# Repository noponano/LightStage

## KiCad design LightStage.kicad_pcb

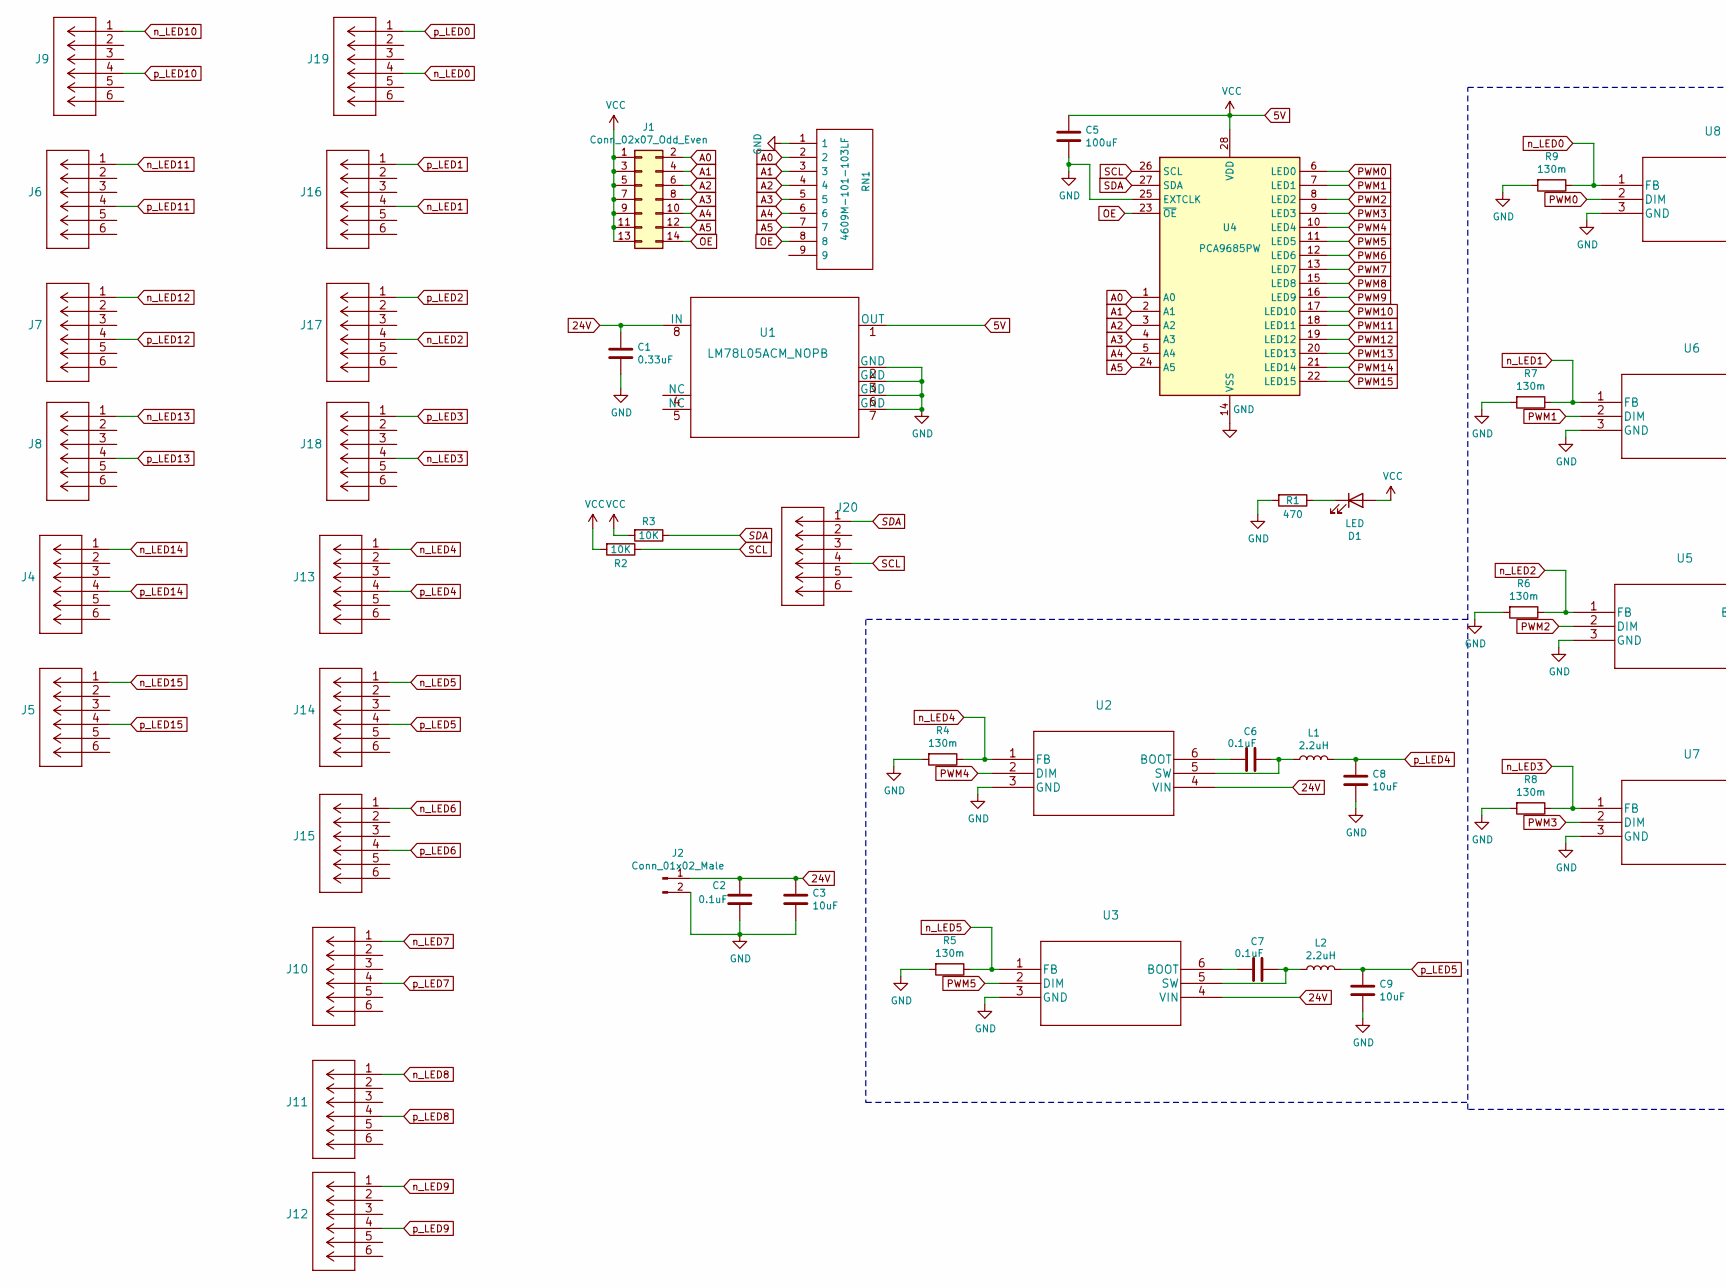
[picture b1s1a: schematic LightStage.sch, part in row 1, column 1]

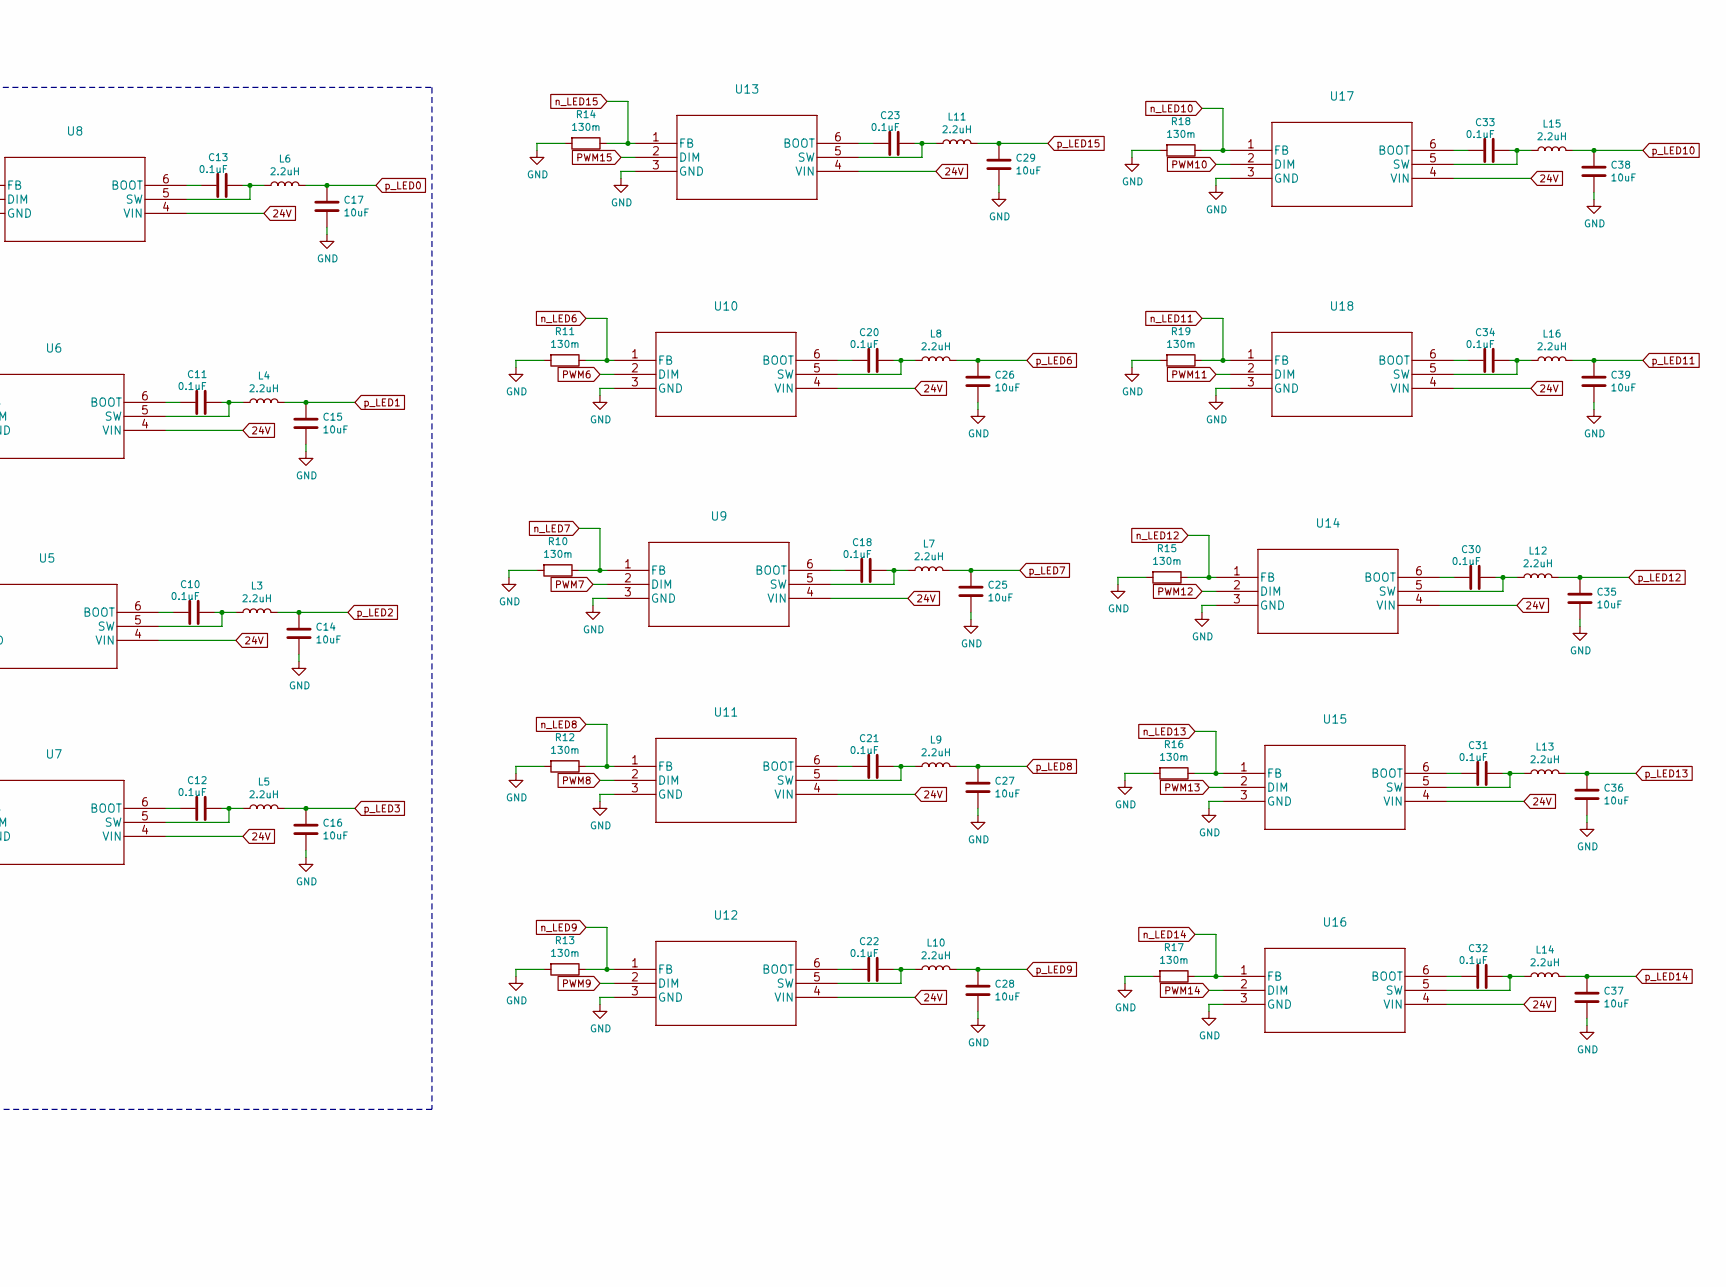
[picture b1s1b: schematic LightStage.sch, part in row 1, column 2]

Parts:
C1: 0.33uF; C_0805_2012Metric_Pad1.18x1.45mm_HandSolder
C2, C6, C7, C10, C11, C12, C13, C18, C20, C21, C22, C23, C30, C31, C32, C33, C34: 0.1uF; C_1206_3216Metric_Pad1.33x1.80mm_HandSolder
C3, C8, C9, C14, C15, C16, C17, C25, C26, C27, C28, C29, C35, C36, C37, C38, C39: 10uF; C_1206_3216Metric_Pad1.33x1.80mm_HandSolder
C5: 100uF; C_1206_3216Metric_Pad1.33x1.80mm_HandSolder
D1: LED; LED_0402_1005Metric_Pad0.77x0.64mm_HandSolder
J1: Conn_02x07_Odd_Even; PinHeader_2x07_P2.54mm_Vertical_SMD
J2: Conn_01x02_Male; Molex_26013114
J4, J5, J6, J7, J8, J9, J10, J11, J12, J13, J14, J15, J16, J17, J18, J19: 781710004
J20: 781710004
L1, L2, L3, L4, L5, L6, L7, L8, L9, L10, L11, L12, L13, L14, L15, L16: 2.2uH; L_0805_2012Metric_Pad1.15x1.40mm_HandSolder
R1: 470; R_0402_1005Metric_Pad0.72x0.64mm_HandSolder
R2, R3: 10K; R_0402_1005Metric_Pad0.72x0.64mm_HandSolder
R4, R5, R6, R7, R8, R9, R10, R11, R12, R13, R14, R15, R16, R17, R18, R19: 130m; R_0603_1608Metric_Pad0.98x0.95mm_HandSolder
RN1: 4609M-101-103LF; 4609X; Mouser Part Number 652-4609M-1LF-10K
U1: LM78L05ACM_NOPB; LM78L05ACM&slash_NOPB
U2, U3, U5, U6, U7, U8, U9, U10, U11, U12, U13, U14, U15, U16, U17, U18: TPS92200D2DDCR
U4: PCA9685PW; TSSOP-28_4.4x9.7mm_P0.65mm

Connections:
5V: C5.1, D1.2 (A), J1.1, J1.3, J1.5, J1.7, J1.9, J1.11, J1.13, R2.2, R3.2, U1.1 (OUT), U4.28 (VDD)
24V: C1.1, C2.1, C3.1, J2.1, U1.8 (IN), U2.4 (VIN), U3.4 (VIN), U5.4 (VIN), U6.4 (VIN), U7.4 (VIN), U8.4 (VIN), U9.4 (VIN), U10.4 (VIN), U11.4 (VIN), U12.4 (VIN), U13.4 (VIN), U14.4 (VIN), U15.4 (VIN), U16.4 (VIN), U17.4 (VIN), U18.4 (VIN)
A0: J1.2, RN1.2, U4.1 (A0)
A1: J1.4, RN1.3, U4.2 (A1)
A2: J1.6, RN1.4, U4.3 (A2)
A3: J1.8, RN1.5, U4.4 (A3)
A4: J1.10, RN1.6, U4.5 (A4)
A5: J1.12, RN1.7, U4.24 (A5)
GND: C1.2, C2.2, C3.2, C5.2, C8.2, C9.2, C14.2, C15.2, C16.2, C17.2, C25.2, C26.2, C27.2, C28.2, C29.2, C35.2, C36.2, C37.2, C38.2, C39.2, J2.2, R1.2, R4.2, R5.2, R6.2, R7.2, R8.2, R9.2, R10.2, R11.2, R12.2, R13.2, R14.2, R15.2, R16.2, R17.2, R18.2, R19.2, RN1.1, U1.2 (GND), U1.3 (GND), U1.6 (GND), U1.7 (GND), U2.3 (GND), U3.3 (GND), U4.14 (VSS), U4.25 (EXTCLK), U5.3 (GND), U6.3 (GND), U7.3 (GND), U8.3 (GND), U9.3 (GND), U10.3 (GND), U11.3 (GND), U12.3 (GND), U13.3 (GND), U14.3 (GND), U15.3 (GND), U16.3 (GND), U17.3 (GND), U18.3 (GND)
unnamed: C6.1, U2.6 (BOOT)
unnamed: C6.2, L1.1, U2.5 (SW)
unnamed: C7.1, U3.6 (BOOT)
unnamed: C7.2, L2.1, U3.5 (SW)
unnamed: C10.1, U5.6 (BOOT)
unnamed: C10.2, L3.1, U5.5 (SW)
unnamed: C11.1, U6.6 (BOOT)
unnamed: C11.2, L4.1, U6.5 (SW)
unnamed: C12.1, U7.6 (BOOT)
unnamed: C12.2, L5.1, U7.5 (SW)
unnamed: C13.1, U8.6 (BOOT)
unnamed: C13.2, L6.1, U8.5 (SW)
unnamed: C18.1, U9.6 (BOOT)
unnamed: C18.2, L7.1, U9.5 (SW)
unnamed: C20.1, U10.6 (BOOT)
unnamed: C20.2, L8.1, U10.5 (SW)
unnamed: C21.1, U11.6 (BOOT)
unnamed: C21.2, L9.1, U11.5 (SW)
unnamed: C22.1, U12.6 (BOOT)
unnamed: C22.2, L10.1, U12.5 (SW)
unnamed: C23.1, U13.6 (BOOT)
unnamed: C23.2, L11.1, U13.5 (SW)
unnamed: C30.1, U14.6 (BOOT)
unnamed: C30.2, L12.1, U14.5 (SW)
unnamed: C31.1, U15.6 (BOOT)
unnamed: C31.2, L13.1, U15.5 (SW)
unnamed: C32.1, U16.6 (BOOT)
unnamed: C32.2, L14.1, U16.5 (SW)
unnamed: C33.1, U17.6 (BOOT)
unnamed: C33.2, L15.1, U17.5 (SW)
unnamed: C34.1, U18.6 (BOOT)
unnamed: C34.2, L16.1, U18.5 (SW)
unnamed: D1.1 (K), R1.1
OE: J1.14, RN1.8, U4.23 (~OE)
PWM0: U4.6 (LED0), U8.2 (DIM)
PWM1: U4.7 (LED1), U6.2 (DIM)
PWM2: U4.8 (LED2), U5.2 (DIM)
PWM3: U4.9 (LED3), U7.2 (DIM)
PWM4: U2.2 (DIM), U4.10 (LED4)
PWM5: U3.2 (DIM), U4.11 (LED5)
PWM6: U4.12 (LED6), U10.2 (DIM)
PWM7: U4.13 (LED7), U9.2 (DIM)
PWM8: U4.15 (LED8), U11.2 (DIM)
PWM9: U4.16 (LED9), U12.2 (DIM)
PWM10: U4.17 (LED10), U17.2 (DIM)
PWM11: U4.18 (LED11), U18.2 (DIM)
PWM12: U4.19 (LED12), U14.2 (DIM)
PWM13: U4.20 (LED13), U15.2 (DIM)
PWM14: U4.21 (LED14), U16.2 (DIM)
PWM15: U4.22 (LED15), U13.2 (DIM)
SCL: J20.4, R2.1, U4.26 (SCL)
SDA: J20.1, R3.1, U4.27 (SDA)
n_LED0: J19.4, R9.1, U8.1 (FB)
n_LED1: J16.4, R7.1, U6.1 (FB)
n_LED2: J17.4, R6.1, U5.1 (FB)
n_LED3: J18.4, R8.1, U7.1 (FB)
n_LED4: J13.1, R4.1, U2.1 (FB)
n_LED5: J14.1, R5.1, U3.1 (FB)
n_LED6: J15.1, R11.1, U10.1 (FB)
n_LED7: J10.1, R10.1, U9.1 (FB)
n_LED8: J11.1, R12.1, U11.1 (FB)
n_LED9: J12.1, R13.1, U12.1 (FB)
n_LED10: J9.1, R18.1, U17.1 (FB)
n_LED11: J6.1, R19.1, U18.1 (FB)
n_LED12: J7.1, R15.1, U14.1 (FB)
n_LED13: J8.1, R16.1, U15.1 (FB)
n_LED14: J4.1, R17.1, U16.1 (FB)
n_LED15: J5.1, R14.1, U13.1 (FB)
p_LED0: C17.1, J19.1, L6.2
p_LED1: C15.1, J16.1, L4.2
p_LED2: C14.1, J17.1, L3.2
p_LED3: C16.1, J18.1, L5.2
p_LED4: C8.1, J13.4, L1.2
p_LED5: C9.1, J14.4, L2.2
p_LED6: C26.1, J15.4, L8.2
p_LED7: C25.1, J10.4, L7.2
p_LED8: C27.1, J11.4, L9.2
p_LED9: C28.1, J12.4, L10.2
p_LED10: C38.1, J9.4, L15.2
p_LED11: C39.1, J6.4, L16.2
p_LED12: C35.1, J7.4, L12.2
p_LED13: C36.1, J8.4, L13.2
p_LED14: C37.1, J4.4, L14.2
p_LED15: C29.1, J5.4, L11.2

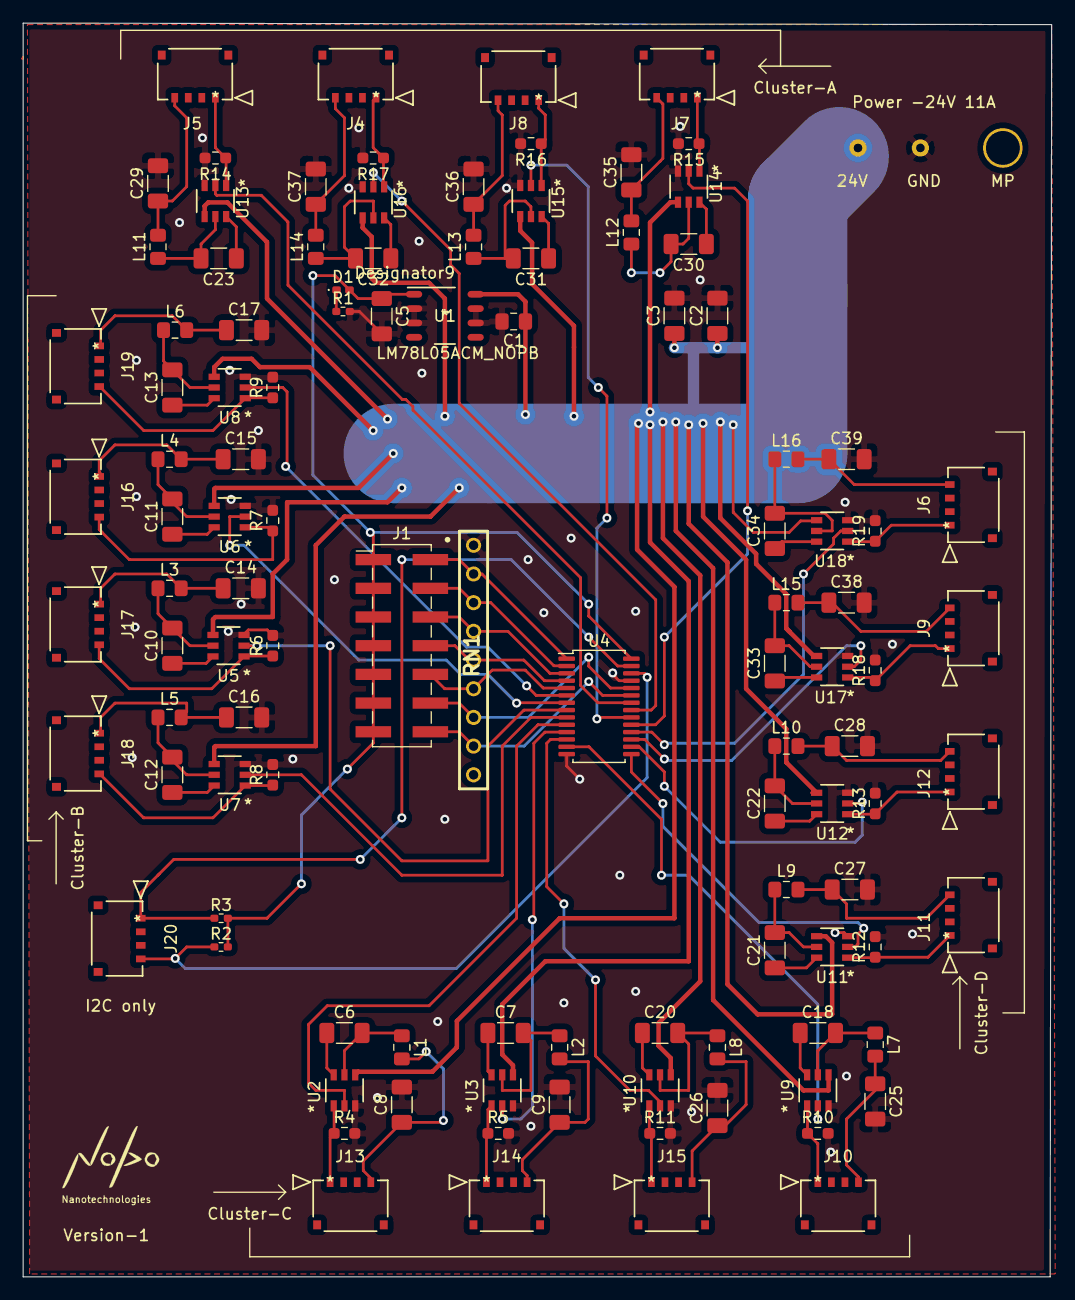
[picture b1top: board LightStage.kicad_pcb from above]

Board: 2 copper layers, 91.1 x 111.0 mm, 111 parts (1 on the bottom side), 93 nets.

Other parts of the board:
 : Logo_NoPo_kicad

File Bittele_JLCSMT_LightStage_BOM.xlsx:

Item | Reference | Quantity | Production Description | Production Mfg | Production P/N | Qty50 | U/P | Ext. Board | Ext. All | Supplier | Global Stock | Supplier PN | Product URL | Notes
1 | C1 | 1 | Cap Ceramic 0.33uF 35V X7R 20% SMD 0805 125°C T/R | Taiyo Yuden | GMK212B7334MG-T | 50 | 7.0999999999999994E-2 | 7.0999999999999994E-2 | 3.55 | Mouser | 8485 | 963-GMK212B7334MG-T | https://octopart.com/click/track?country=US&ct=offers&ppid=7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
2 | C2, C6, C7, C10, C11, C12, C13, C18, C20, C21, C22, C23, C30, C31, C32, C33, C34 | 17 | 0.1uF | KEMET | C1206C104K6RACTU | 850 | 0.09 | 1.53 | 76.5 | Mouser | 4715 | 80-C1206C104K6RACTU | https://octopart.com/click/track?country=US&ct=offers&ppid=8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
3 | C3, C8, C9, C14, C15, C16, C17, C25, C26, C27, C28, C29, C35, C36, C37, C38, C39 | 17 | Multilayer Ceramic Capacitors MLCC - SMD/SMT 10uF 35V X7R +/-10% 1206 Gen Purp | Taiyo Yuden | GMK316AB7106KL-TR | 850 | 0.187 | 3.1789999999999998 | 158.94999999999999 | Digi-Key | 914365 | 587-3007-1-ND | https://octopart.com/click/track?country=US&ct=offers&ppid=2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
4 | C5 | 1 | Cap Ceramic 100uF 10V X5R 20% SMD 1206 85°C Embossed T/R |  |  | 50 | 0.67 | 0.67 | 33.5 | Digi-Key |  |  | https://www.digikey.com/en/products/detail/tdk-corporation/C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
5 | D1 | 1 | Led Green Clear 0402 SMD | Würth Elektronik | 150040GS73240 | 50 | 0.254 | 0.254 | 12.7 | Digi-Key | 17337 | 732-11990-1-ND | https://octopart.com/click/track?country=US&ct=offers&ppid=9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
6 | J1 | 1 | Connector, Header, 14POS, 2ROW, 1.27MM | Harwin | M50-3610742R | 50 | 1.52 | 1.52 | 76 | Mouser | 2397 | 855-M50-3610742R | https://octopart.com/click/track?country=US&ct=offers&ppid=7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
7 | J2 | 1 | Conn Power HDR 2 POS Solder RA Thru-Hole 2 Terminal 1 Port Mini-Fit Jr™ Bag | Molex | 26-01-3114 | 50 | 0.72699999999999998 | 0.72699999999999998 | 36.35 | Mouser | 34573 | 538-26-01-3114 | https://octopart.com/click/track?country=US&ct=offers&ppid=2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
8 | J4, J5, J6, J7, J8, J9, J10, J11, J12, J13, J14, J15, J16, J17, J18, J19 | 16 | 1.20mm Pitch, Pico-EZmate PCB Header, Single Row, Gold Plating, Friction Lock, 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 | Molex | 78171-0004 | 800 | 0.32700000000000001 | 5.2320000000000002 | 261.60000000000002 | Chip 1 Stop - An Arrow Company | Custom Vendor | C1S516500496253 | https://www.chip1stop.com/view/dispDetail/DispDetail?partId=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;ut…
9 | J20 | 1 | 1.20mm Pitch, Pico-EZmate PCB Header, Single Row, Gold Plating, Friction Lock, 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 | Molex | 781710004 | 50 | 0.32700000000000001 | 0.32700000000000001 | 16.350000000000001 | Chip 1 Stop - An Arrow Company | Custom Vendor | 78171-0004 | https://www.chip1stop.com/view/dispDetail/DispDetail?partId=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;ut… | Same as other custom part.
10 | L1, L2, L3, L4, L5, L6, L7, L8, L9, L10, L11, L12, L13, L14, L15, L16 | 16 | Inductor Power Chip Wirewound 2.2uH 20% 1MHz Ferrite 1A 0.143Ohm DCR 0805 T/R | Taiyo Yuden | BRC2012T2R2MD | 800 | 0.15744 | 2.5190399999999999 | 125.952 | Digi-Key | 110746 | 587-2905-1-ND | https://octopart.com/click/track?country=US&ct=offers&ppid=2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
11 | R1 | 1 | Res Thin Film 0402 470 Ohm 0.1% 1/16W ±25ppm/°C Molded SMD SMD Paper T/R | TE Connectivity | CPF0402B470RE1 | 50 | 0.371 | 0.371 | 18.55 | Mouser | 2107 | 279-CPF0402B470RE1 | https://octopart.com/click/track?country=US&ct=offers&ppid=9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
12 | R2, R3 | 2 | Resistor Thick Film Chip 10kOhm1% 2-Pin 1005 T/R | Bourns | CR01005-FW-1002GLF | 100 | 2.8799999999999999E-2 | 5.7599999999999998E-2 | 2.88 | Digi-Key | 44498 | 118-CR01005-FW-1002GLFCT-ND | https://octopart.com/click/track?country=US&ct=offers&ppid=1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
13 | R4, R5, R6, R7, R8, R9, R10, R11, R12, R13, R14, R15, R16, R17, R18, R19 | 16 | Res High Power Current Sense Thick Film 0603 0.13 Ohm 5% 1/8W ±300ppm/°C Molded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 | TE Connectivity | RLP73N1JR13JTD | 800 | 6.5000000000000002E-2 | 1.04 | 52 | Mouser | 3987 | 279-RLP73N1JR13JTD | https://octopart.com/click/track?country=US&ct=offers&ppid=4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
14 | RN1 | 1 | Res Thick Film NET 10K Ohm 2% 1.35W ±100ppm/°C BUS Conformal 9-Pin SIP Pin Thru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 | Bourns | 4609M-101-103LF | 50 | 0.378 | 0.378 | 18.899999999999999 | Digi-Key | 17060 | 4609M-101-103LF-ND | https://octopart.com/click/track?country=US&ct=offers&ppid=1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
15 | U1 | 1 | 100-mA, 30-V, linear voltage regulator 8-SOIC 0 to 125 | Texas Instruments | LM78L05ACM/NOPB | 50 | 0.50419999999999998 | 0.50419999999999998 | 25.21 | Arrow Electronics | 941 | LM78L05ACM/NOPB | https://octopart.com/click/track?country=US&ct=offers&ppid=2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
16 | U2, U3, U5, U6, U7, U8, U9, U10, U11, U12, U13, U14, U15, U16, U17, U18 | 16 | 4-V to 30-V input voltage, 1.5-A output current, synchronous buck LED driver wi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 | Texas Instruments | TPS92200D1DDCR | 800 | 0.38159999999999999 | 6.1055999999999999 | 305.27999999999997 | Digi-Key | 3144 | 296-TPS92200D1DDCRCT-ND | https://octopart.com/click/track?country=US&ct=offers&ppid=1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
17 | U4 | 1 | PCA9685 Series 25 mA 5.5 V 1 MHz 12-bit PWM Fm+I2C-Bus LED Controller - TSSOP-28 | NXP Semiconductors | PCA9685PW,112 | 50 | 1.92 | 1.92 | 96 | Newark | 3541 | 85AC2130 | https://octopart.com/click/track?country=US&ct=offers&ppid=1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
 |  |  |  |  |  | Sub-Total |  | 26.405439999999999 | 1320.2719999999999
 |  |  |  |  |  | Production Loss |  | 1.0562175999999999 | 52.810879999999997
 |  |  |  |  |  | Shipping Cost |  | 0 | 0
 |  |  |  |  |  | PARTS TOTAL | PARTS TOTAL | 27.461657599999999 | 1373.0828799999999
 |  |  |  |  |  | All prices are in USD

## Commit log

2021-03-29 Light Stage version 2
    Light Stage
2021-03-29 LightStage Version 2 with all comp on Top
2021-04-08 The updated kicad drawings

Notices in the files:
parts and their libraries:
Copyright 2016 Accelerated Designs. All rights reserved.
